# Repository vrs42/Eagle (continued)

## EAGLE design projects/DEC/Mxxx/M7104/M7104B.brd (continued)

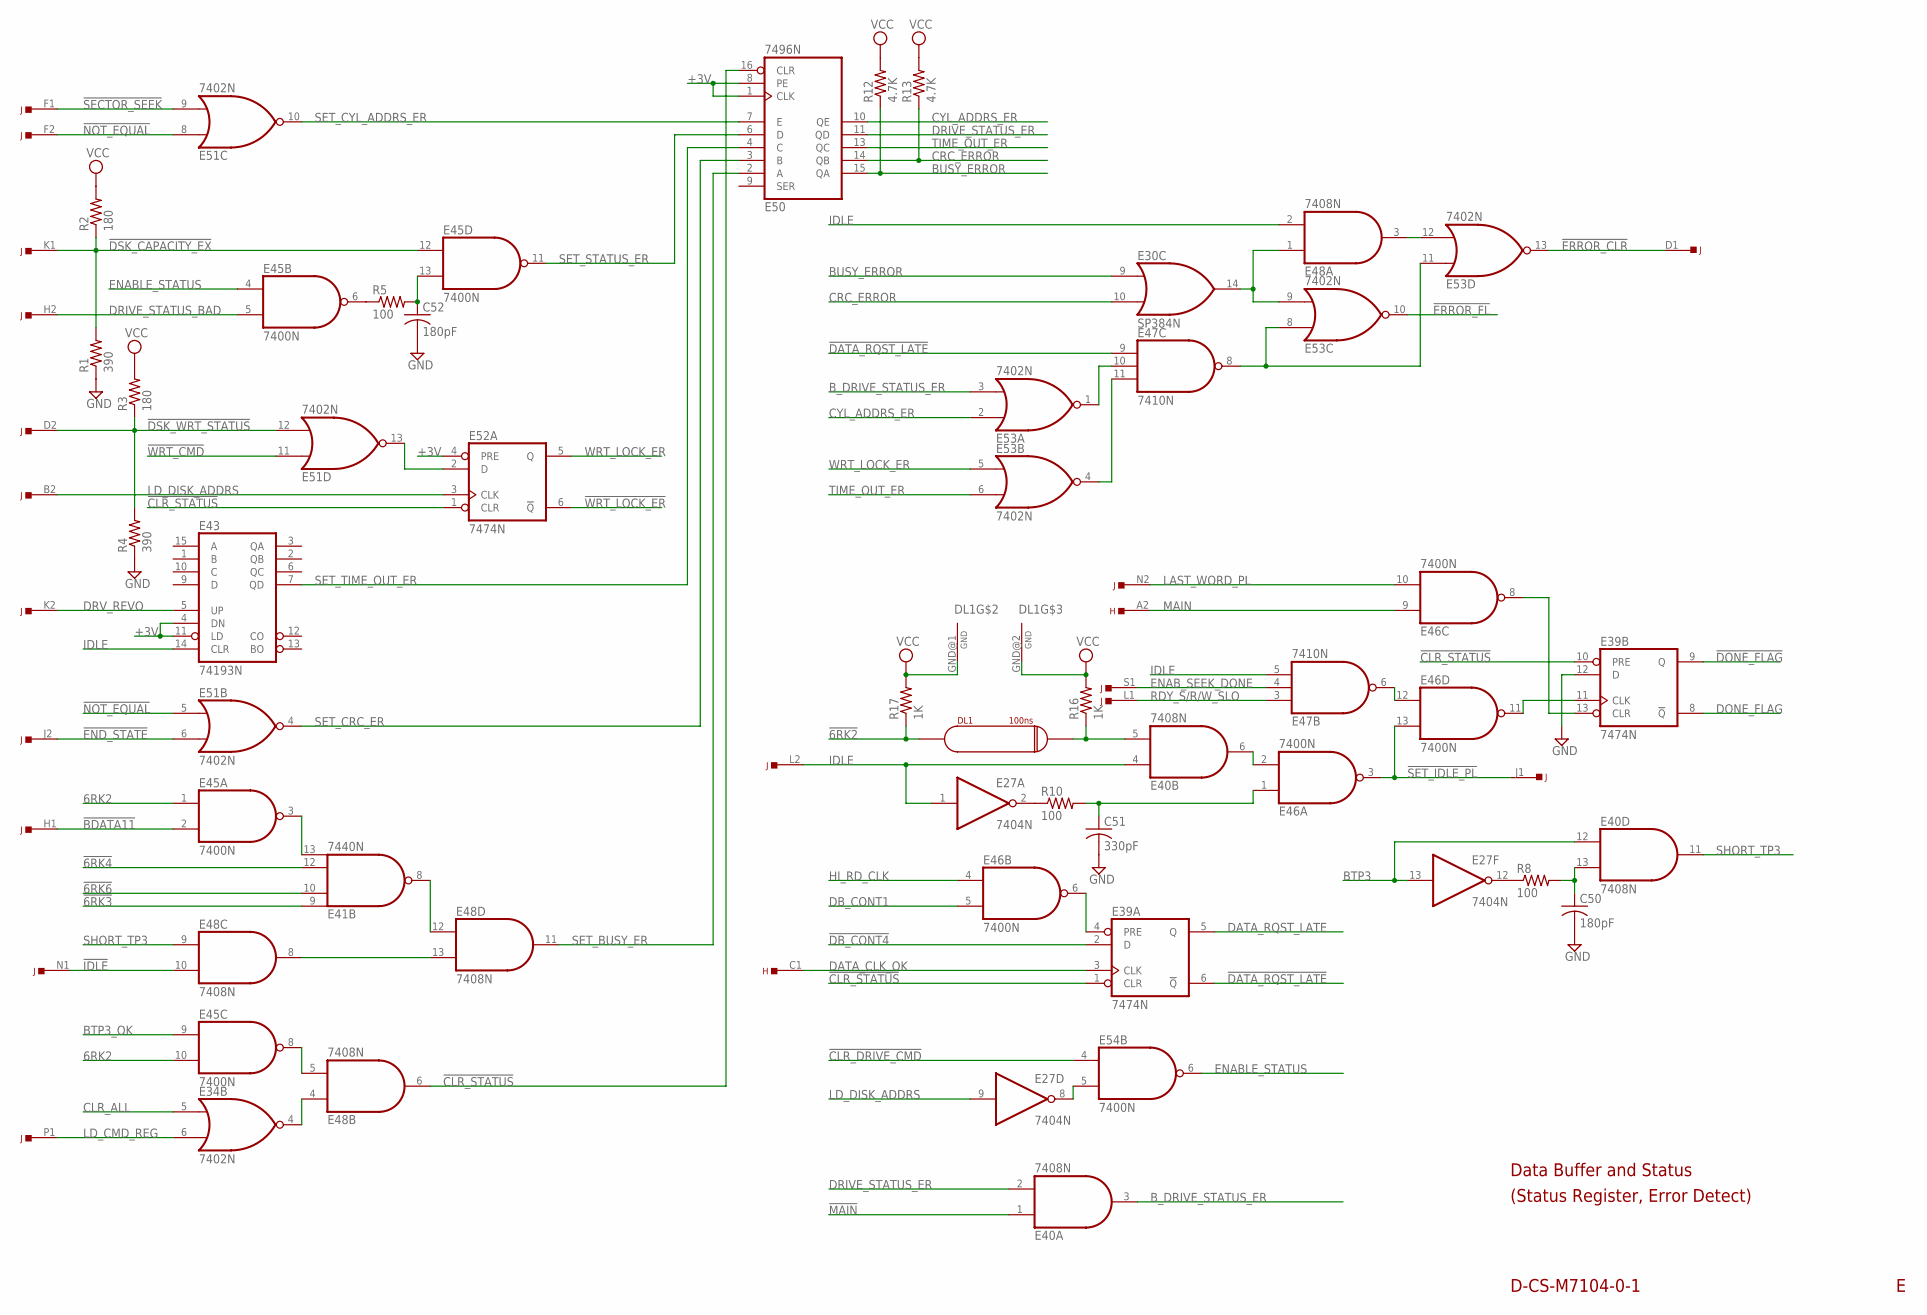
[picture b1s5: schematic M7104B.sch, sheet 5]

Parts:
C50, C52: 180pF; C063-025X075
C51: 330pF; C063-025X075
DL1: 100ns; RCL-L-XX-22
E27: 7404N; DIL14
E30: SP384N; DIL14
E34, E51, E53: 7402N; DIL14
E39, E52: 7474N; DIL14
E40, E48: 7408N; DIL14
E41: 7440N; DIL14
E43: 74193N; DIL16
E45, E46, E54: 7400N; DIL14
E47: 7410N; DIL14
E50: 7496N; DIL16
H: EDGE-TOP; EDGE-CON2
J: EDGE-TOP; EDGE-CON2
R1, R4: 390; 0207/10
R2, R3: 180; 0207/10
R5, R8, R10: 100; 0207/10
R12, R13: 4.7K; 0207/10
R16, R17: 1K; 0207/10

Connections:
6RK2: E45.1 (I0), E45.10 (I1); also elsewhere on the board
!6RK2: DL1.IN, R17.1; also elsewhere on the board
!6RK3: E41.9 (I0); also elsewhere on the board
!6RK4: E41.12 (I2); also elsewhere on the board
!6RK6: E41.10 (I1); also elsewhere on the board
!BDATA11: E45.2 (I1), J.H1; also elsewhere on the board
!CLR_DRIVE_CMD: E54.4 (I0); also elsewhere on the board
!CLR_STATUS: E39.1 (CLR), E39.10 (PRE), E48.6 (O), E50.16 (CLR), E52.1 (CLR)
!DATA_RQST_LATE: E39.6 (!Q), E47.9 (I0)
!DB_CONT4: E39.2 (D); also elsewhere on the board
!DONE_FLAG: E39.9 (Q); also elsewhere on the board
!DSK_CAPACITY_EX: E45.12 (I0), J.K1, R1.2, R2.1
!DSK_WRT_STATUS: E51.12 (I1), J.D2, R3.1, R4.2
!END_STATE: E51.6 (I1), J.J2
!ERROR_CLR: E53.13 (O), J.D1
!ERROR_FL: E53.10 (O); also elsewhere on the board
!IDLE: E48.10 (I1), J.N1; also elsewhere on the board
!MAIN: E40.1 (I0); also elsewhere on the board
!NOT_EQUAL: E51.5 (I0), E51.8 (I0), J.F2
!SECTOR_SEEK: E51.9 (I1), J.F1
!SET_IDLE_PL: E46.3 (O), E46.13 (I1), J.J1
!WRT_CMD: E51.11 (I0); also elsewhere on the board
!WRT_LOCK_ER: E52.6 (!Q)
+3V: E43.4 (DN), E43.11 (LD), E50.1 (CLK), E50.8 (PE), E52.4 (PRE); also elsewhere on the board
BTP3: E27.13 (I), E40.12 (I0); also elsewhere on the board
BTP3_OK: E45.9 (I0); also elsewhere on the board
BUSY_ERROR: E30.9 (I0), E50.15 (QA), R12.1; also elsewhere on the board
B_DRIVE_STATUS_ER: E40.3 (O), E53.3 (I1)
CLR_ALL: E34.5 (I0); also elsewhere on the board
CRC_ERROR: E30.10 (I1), E50.14 (QB), R13.1; also elsewhere on the board
CYL_ADDRS_ER: E50.10 (QE), E53.2 (I0); also elsewhere on the board
DATA_CLK_OK: E39.3 (CLK), H.C1
DATA_RQST_LATE: E39.5 (Q); also elsewhere on the board
DB_CONT1: E46.5 (I1); also elsewhere on the board
DONE_FLAG: E39.8 (!Q); also elsewhere on the board
DRIVE_STATUS_BAD: E45.5 (I1), J.H2
DRIVE_STATUS_ER: E40.2 (I1), E50.11 (QD); also elsewhere on the board
DRV_REVO: E43.5 (UP), J.K2
ENABLE_STATUS: E45.4 (I0), E54.6 (O)
ENAB_SEEK_DONE: E47.4 (I1), J.S1
GND: C50.2, C51.2, C52.2, E27.7 (GND), E30.1 (GND), E34.7 (GND), E39.7 (GND), E39.12 (D), E40.7 (GND), E41.7 (GND), E43.8 (GND), E45.7 (GND), E46.7 (GND), E47.7 (GND), E48.7 (GND), E50.12 (GND), E51.7 (GND), E52.7 (GND), E53.7 (GND), E54.7 (GND), R1.1, R4.1; also elsewhere on the board
HI_RD_CLK: E46.4 (I0); also elsewhere on the board
IDLE: E27.1 (I), E40.4 (I0), E43.14 (CLR), E47.5 (I2), E48.2 (I1), J.L2; also elsewhere on the board
LAST_WORD_PL: E46.10 (I1), J.N2
LD_CMD_REG: E34.6 (I1), J.P1
LD_DISK_ADDRS: E27.9 (I), E52.3 (CLK), J.B2
MAIN: E46.9 (I0), H.A2; also elsewhere on the board
unnamed: E45.6 (O), R5.1
unnamed: C52.1, E45.13 (I1), R5.2
unnamed: C51.1, E46.1 (I0), R10.2
unnamed: E51.13 (O), E52.2 (D)
unnamed: E41.13 (I3), E45.3 (O)
unnamed: E41.8 (O), E48.12 (I0)
unnamed: E40.6 (O), E46.2 (I1)
unnamed: DL1.OUT, E40.5 (I1), R16.1
unnamed: E48.8 (O), E48.13 (I1)
unnamed: E45.8 (O), E48.5 (I1)
unnamed: E34.4 (O), E48.4 (I0)
unnamed: E47.11 (I2), E53.4 (O)
unnamed: E47.10 (I1), E53.1 (O)
unnamed: E30.14 (O), E48.1 (I0), E53.9 (I1)
unnamed: E47.8 (O), E53.8 (I0), E53.11 (I0)
unnamed: E48.3 (O), E53.12 (I1)
unnamed: E27.2 (O), R10.1
unnamed: E46.12 (I0), E47.6 (O)
unnamed: E39.11 (CLK), E46.11 (O)
unnamed: E39.13 (CLR), E46.8 (O)
unnamed: E39.4 (PRE), E46.6 (O)
unnamed: E27.8 (O), E54.5 (I1)
unnamed: E27.12 (O), R8.1
unnamed: C50.1, E40.13 (I1), R8.2
RDY_S/R/W_SLO: E47.3 (I0), J.L1
SET_BUSY_ER: E48.11 (O), E50.2 (A)
SET_CRC_ER: E50.3 (B), E51.4 (O)
SET_CYL_ADDRS_ER: E50.7 (E), E51.10 (O)
SET_STATUS_ER: E45.11 (O), E50.6 (D)
SET_TIME_OUT_ER: E43.7 (QD), E50.4 (C)
SHORT_TP3: E40.11 (O), E48.9 (I0)
TIME_OUT_ER: E50.13 (QC), E53.6 (I1); also elsewhere on the board
VCC: DL1.GND@1 (GND), DL1.GND@2 (GND), E27.14 (VCC), E30.8 (VCC), E34.14 (VCC), E39.14 (VCC), E40.14 (VCC), E41.14 (VCC), E43.16 (VCC), E45.14 (VCC), E46.14 (VCC), E47.14 (VCC), E48.14 (VCC), E50.5 (VCC), E51.14 (VCC), E52.14 (VCC), E53.14 (VCC), E54.14 (VCC), R2.2, R3.2, R12.2, R13.2, R16.2, R17.2; also elsewhere on the board
WRT_LOCK_ER: E52.5 (Q), E53.5 (I0); also elsewhere on the board

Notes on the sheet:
Data Buffer and Status
D-CS-M7104-0-1
(Status Register, Error Detect)

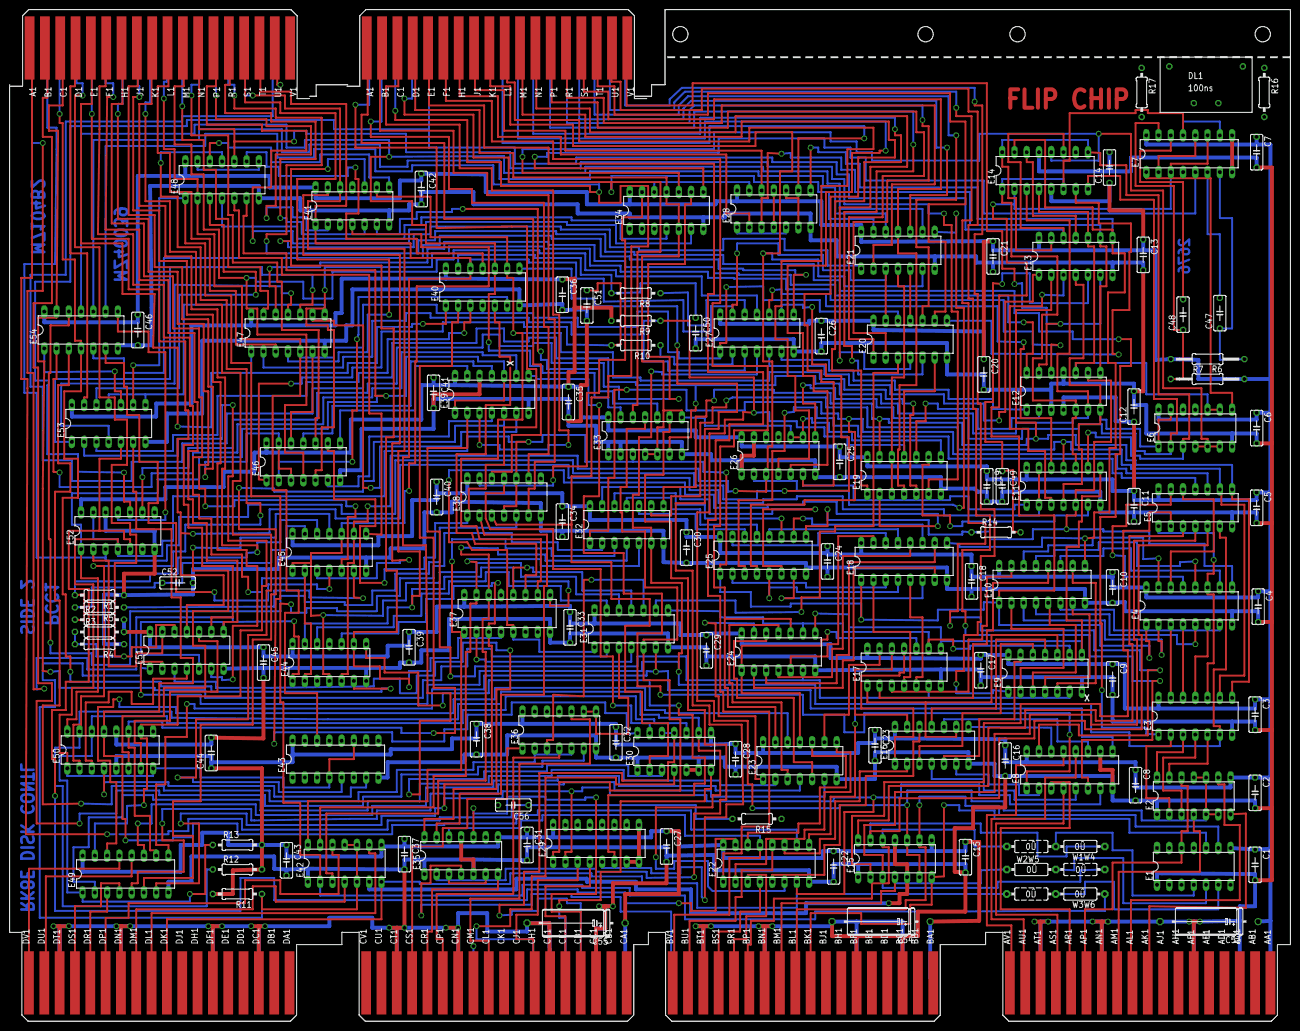
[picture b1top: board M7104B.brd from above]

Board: 4 copper layers, 265.3 x 209.6 mm, 134 parts (0 on the bottom side), 292 nets.

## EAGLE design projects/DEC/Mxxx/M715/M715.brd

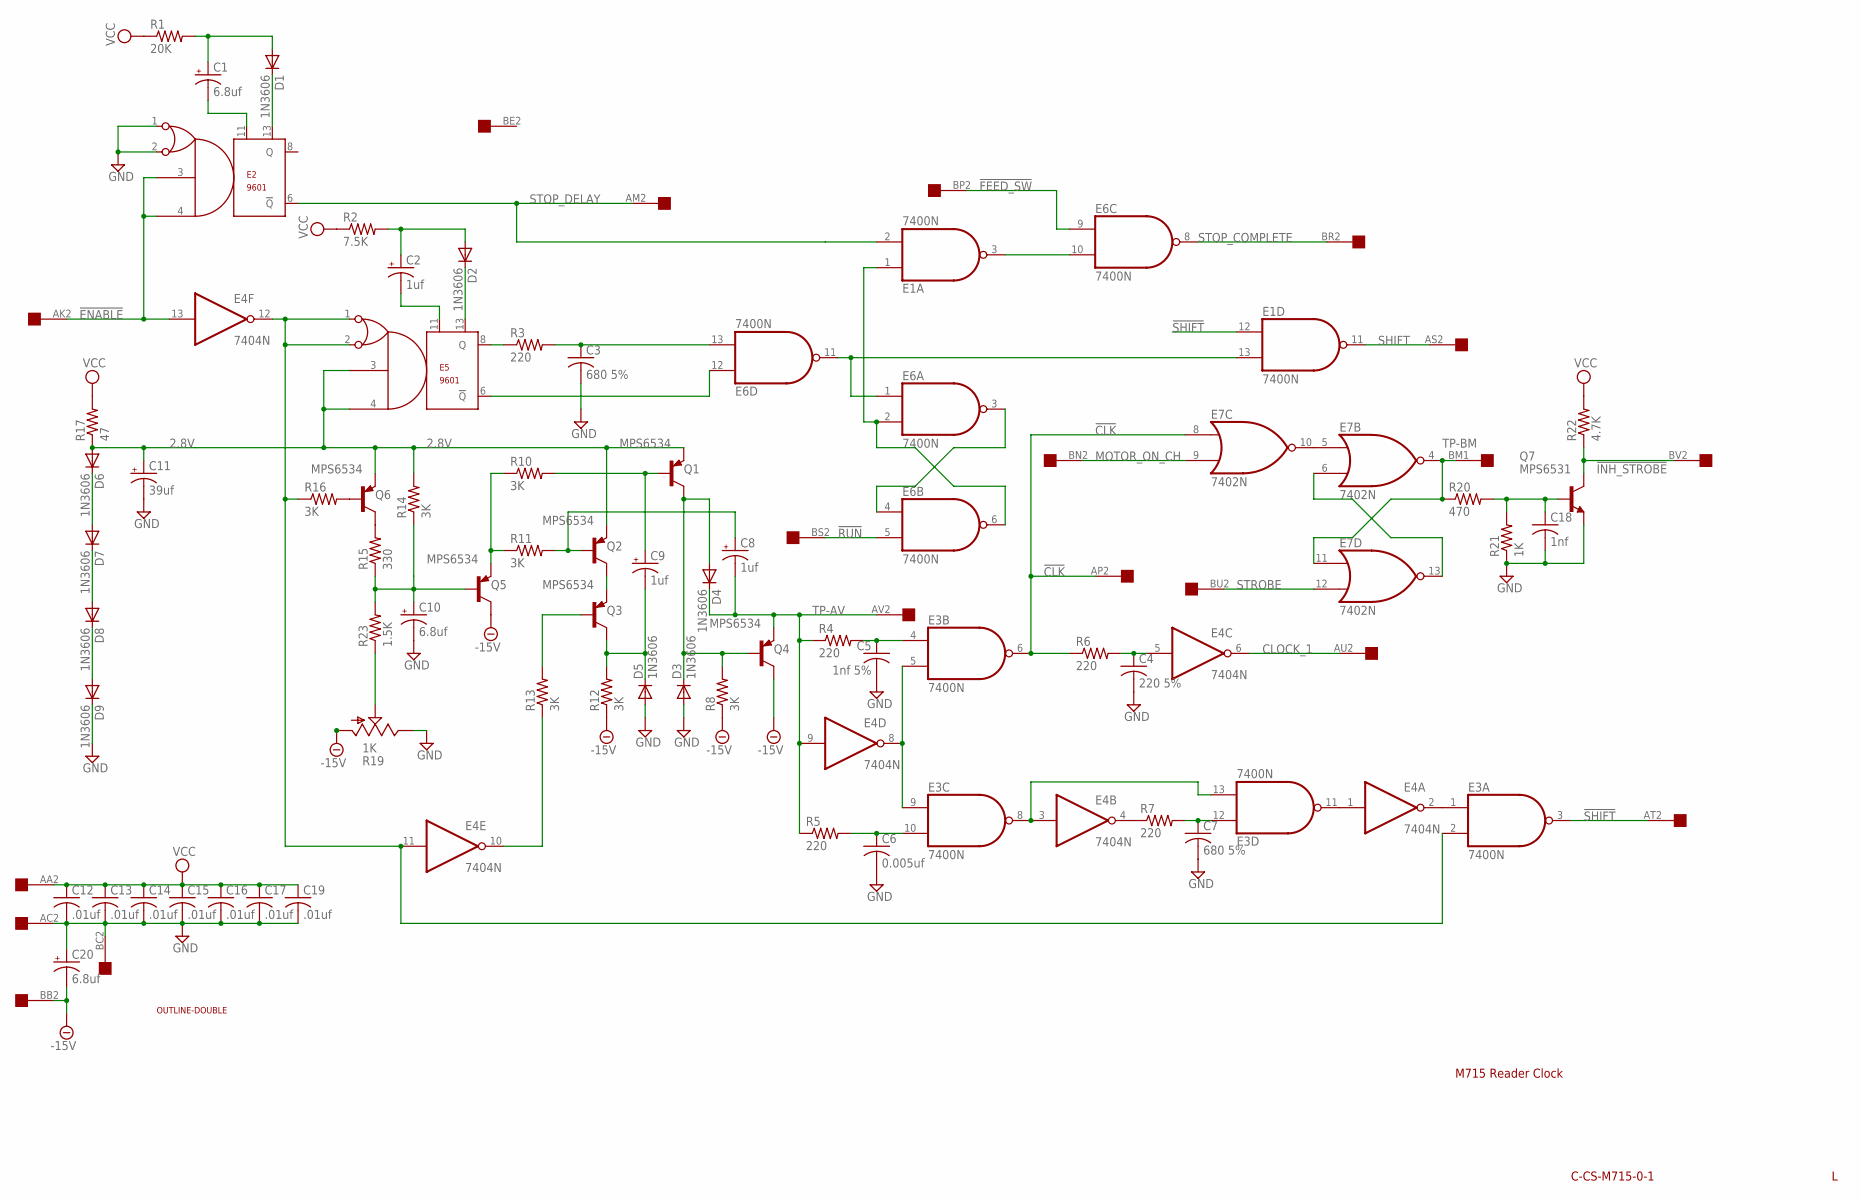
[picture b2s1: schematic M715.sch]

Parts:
C1, C10, C20: 6.8uf; E22-6
C2, C8, C9: 1uf; E15-5
C3, C7: 680 5%; C050-025X075
C4: 220 5%; C050-025X075
C5: 1nf 5%; C050-025X075
C6: 0.005uf; C050-025X075
C11: 39uf; E22-6
C12, C13, C14, C15, C16, C17, C19: .01uf; C050-025X075
C18: 1nf; C050-025X075
D1, D2, D3, D4, D5, D6, D7, D8, D9: 1N3606; DO35-10
E1, E3, E6: 7400N; DIL14
E2, E5: 9601; DIL14
E4: 7404N; DIL14
E7: 7402N; DIL14
Q1, Q2, Q3, Q4, Q5, Q6: MPS6534; TO92
Q7: MPS6531; TO92
R1: 20K; 0207/10
R2: 7.5K; 0207/10
R3, R4, R5, R6, R7: 220; 0207/10
R8, R10, R11, R12, R13, R14, R16: 3K; 0207/10
R15: 330; 0207/10
R17: 47; 0207/10
R19: 1K; PT-SPIN
R20: 470; 0207/10
R21: 1K; 0207/10
R22: 4.7K; 0207/10
R23: 1.5K; 0207/10
U$1: DOUBLE; EDGE-CON4
U$2: OUTLINE-DOUBLE; DOUBLE

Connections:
2.8V: C11.+, D6.A, E5.3, E5.4, Q1.1 (E), Q2.1 (E), Q6.1 (E), R14.2, R17.1
!CLK: E3.6 (O), E7.8 (I0), R6.1, U$1.AP2
!ENABLE: E2.3, E2.4, E4.13 (I), U$1.AK2
!FEED_SW: E6.9 (I0), U$1.BP2
!INH_STROBE: Q7.3 (C), R22.1, U$1.BV2
!RUN: E6.5 (I1), U$1.BS2
!SHIFT: E1.12 (I0), E3.3 (O), U$1.AT2
-15V: C20.-, Q4.3 (C), Q5.3 (C), R8.1, R12.1, R19.A, U$1.BB2
CLOCK_1: E4.6 (O), U$1.AU2
GND: C3.2, C4.2, C5.2, C6.2, C7.2, C10.-, C11.-, C12.2, C13.2, C14.2, C15.2, C16.2, C17.2, C18.2, C19.2, C20.+, D3.A, D5.A, D9.C, E1.7 (GND), E2.1, E2.2, E2.7 (GND), E3.7 (GND), E4.7 (GND), E5.7 (GND), E6.7 (GND), E7.7 (GND), Q7.1 (E), R19.E, R21.1, U$1.AC2, U$1.BC2
MOTOR_ON_CH: E7.9 (I1), U$1.BN2
unnamed: E6.3 (O), E6.4 (I0)
unnamed: E1.1 (I0), E6.2 (I1), E6.6 (O)
unnamed: E1.13 (I1), E6.1 (I0), E6.11 (O)
unnamed: E3.1 (I0), E4.2 (O)
unnamed: E7.6 (I1), E7.13 (O)
unnamed: E1.3 (O), E6.10 (I1)
unnamed: Q6.2 (B), R16.2
unnamed: E7.5 (I0), E7.10 (O)
unnamed: E3.2 (I1), E4.11 (I), E4.12 (O), E5.1, E5.2, R16.1
unnamed: E3.5 (I1), E3.9 (I0), E4.8 (O)
unnamed: E3.11 (O), E4.1 (I)
unnamed: E3.8 (O), E3.13 (I1), E4.3 (I)
unnamed: C7.1, E3.12 (I0), R7.2
unnamed: E4.4 (O), R7.1
unnamed: R19.S, R23.1
unnamed: C4.1, E4.5 (I), R6.2
unnamed: C18.1, Q7.2 (B), R20.2, R21.2
unnamed: C6.1, E3.10 (I1), R5.2
unnamed: C5.1, E3.4 (I0), R4.2
unnamed: D6.C, D7.A
unnamed: D7.C, D8.A
unnamed: D8.C, D9.A
unnamed: Q6.3 (C), R15.2
unnamed: C10.+, Q5.2 (B), R14.1, R15.1, R23.2
unnamed: Q5.1 (E), R10.1, R11.1
unnamed: Q2.3 (C), Q3.1 (E)
unnamed: C8.+, Q2.2 (B), R11.2
unnamed: E4.10 (O), R13.1
unnamed: Q3.2 (B), R13.2
unnamed: C9.-, D5.C, Q3.3 (C), R12.2
unnamed: C9.+, Q1.2 (B), R10.2
unnamed: D3.C, D4.A, Q1.3 (C), Q4.2 (B), R8.2
unnamed: D1.C, E2.13
unnamed: C1.-, E2.11
unnamed: C1.+, D1.A, R1.2
unnamed: D2.C, E5.13
unnamed: C2.-, E5.11
unnamed: C2.+, D2.A, R2.2
unnamed: E5.6 (!Q), E6.12 (I0)
unnamed: E5.8 (Q), R3.1
unnamed: C3.1, E6.13 (I1), R3.2
SHIFT: E1.11 (O), U$1.AS2
STOP_COMPLETE: E6.8 (O), U$1.BR2
STOP_DELAY: E1.2 (I1), E2.6 (!Q), U$1.AM2
STROBE: E7.12 (I1), U$1.BU2
TP-AV: C8.-, D4.C, E4.9 (I), Q4.1 (E), R4.1, R5.1, U$1.AV2
TP-BM: E7.4 (O), E7.11 (I0), R20.1, U$1.BM1
VCC: C12.1, C13.1, C14.1, C15.1, C16.1, C17.1, C19.1, E1.14 (VCC), E2.14 (VCC), E3.14 (VCC), E4.14 (VCC), E5.14 (VCC), E6.14 (VCC), E7.14 (VCC), R1.1, R2.1, R17.2, R22.2, U$1.AA2

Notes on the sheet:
M715 Reader Clock
C-CS-M715-0-1

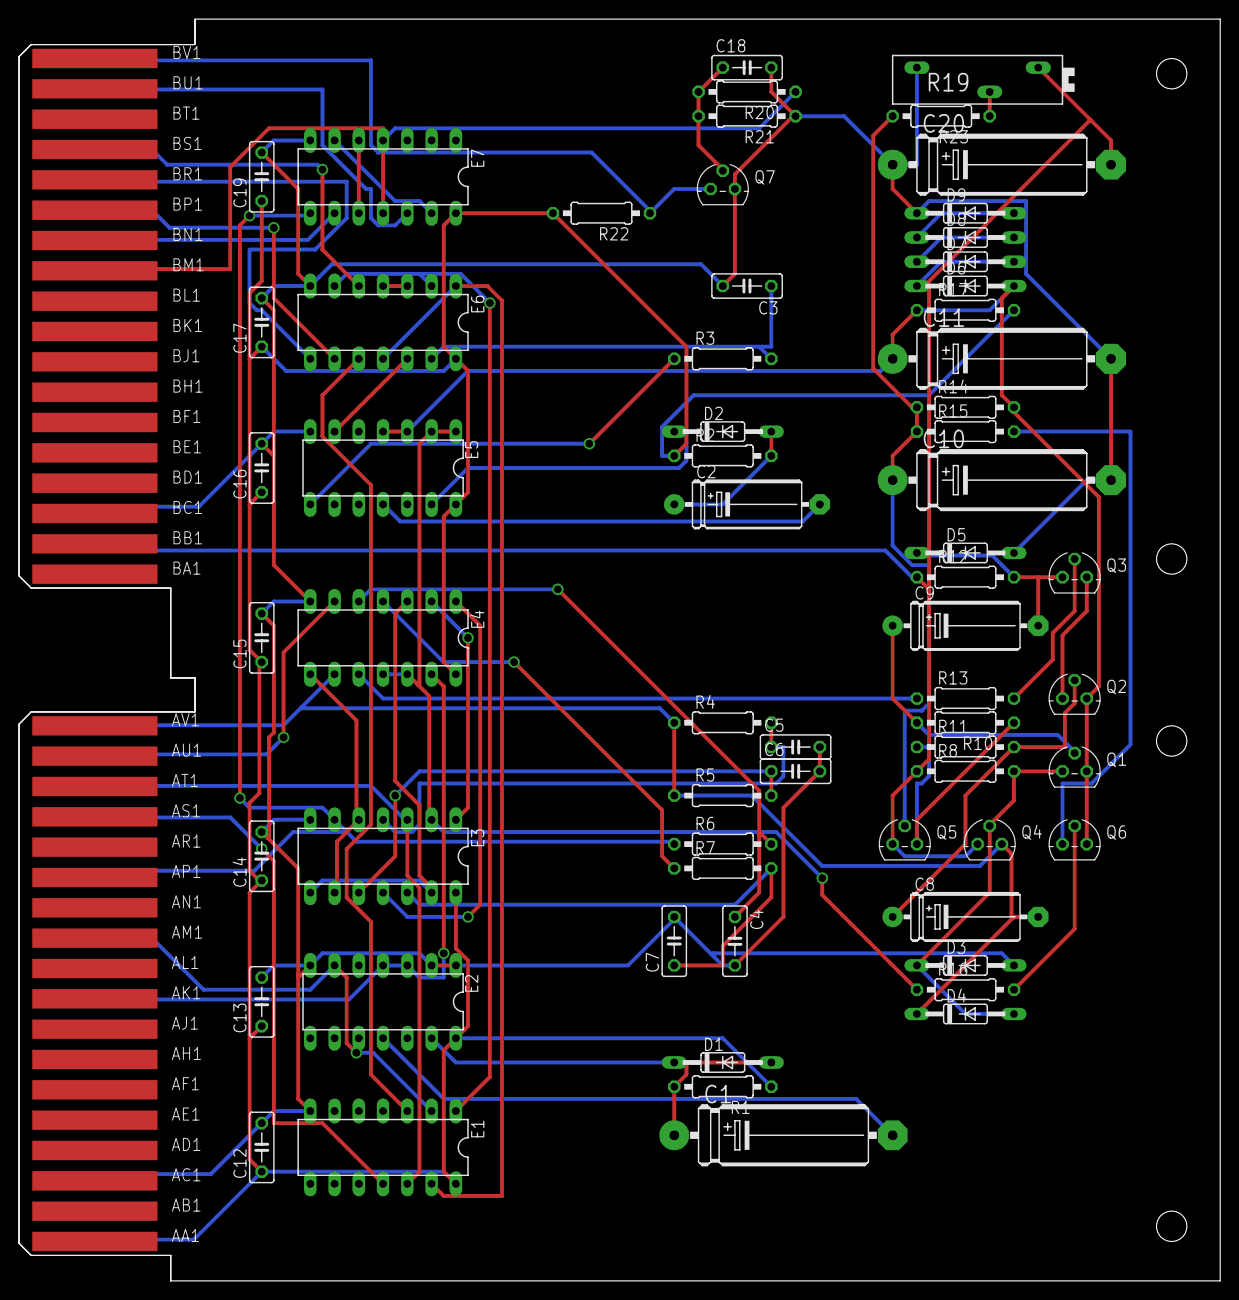
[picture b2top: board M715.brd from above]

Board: 2 copper layers, 125.7 x 132.1 mm, 66 parts (0 on the bottom side), 59 nets.

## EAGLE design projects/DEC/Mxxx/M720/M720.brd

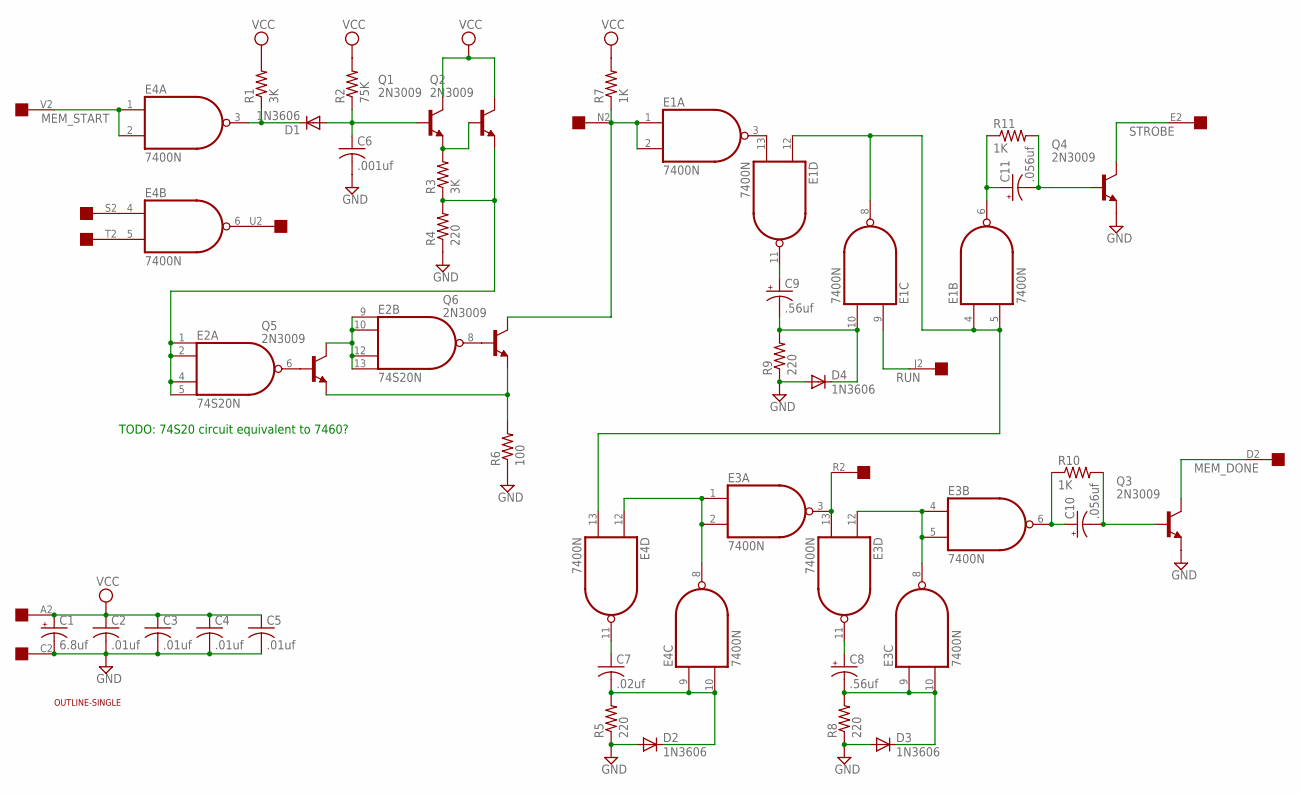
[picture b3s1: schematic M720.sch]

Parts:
C1: 6.8uf; E15-5
C2, C3, C4, C5: .01uf; C050-025X075
C6: .001uf; C050-025X075
C7: .02uf; C050-025X075
C8, C9: .56uf; B45181C
C10, C11: .056uf; B45181C
D1, D2, D3, D4: 1N3606; DO35-10
E1, E3, E4: 7400N; DIL14
E2: 74S20N; DIL14
Q1, Q2, Q3, Q4, Q5, Q6: 2N3009; TO5
R1, R3: 3K; 0207/10
R2: 75K; 0207/10
R4, R5, R8, R9: 220; 0207/10
R6: 100; 0207/10
R7, R10, R11: 1K; 0207/10
U$1: OUTLINE-SINGLE; SINGLE
U$3: EDGE-1; EDGE-CON1

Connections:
GND: C1.-, C2.2, C3.2, C4.2, C5.2, C6.2, D2.A, D3.A, D4.A, E1.7 (GND), E2.7 (GND), E3.7 (GND), E4.7 (GND), Q3.1 (E), Q4.1 (E), R4.1, R5.1, R6.1, R8.1, R9.1, U$3.C2
MEM_DONE: Q3.3 (C), U$3.D2
MEM_START: E4.1 (I0), E4.2 (I1), U$3.V2
unnamed: E2.1 (I0), E2.2 (I1), E2.4 (I2), E2.5 (I3), Q2.1 (E), R3.1, R4.2
unnamed: D1.C, E4.3 (O), R1.1
unnamed: C6.1, D1.A, Q1.2 (B), R2.1
unnamed: Q1.1 (E), Q2.2 (B), R3.2
unnamed: E4.4 (I0), U$3.S2
unnamed: E4.5 (I1), U$3.T2
unnamed: E4.6 (O), U$3.U2
unnamed: E1.1 (I0), E1.2 (I1), Q6.3 (C), R7.1, U$3.N2
unnamed: E1.3 (O), E1.13 (I1)
unnamed: E1.4 (I0), E1.5 (I1), E1.8 (O), E1.12 (I0), E4.13 (I1)
unnamed: C7.2, D2.C, E4.9 (I0), E4.10 (I1), R5.2
unnamed: C9.+, E1.11 (O)
unnamed: C9.-, D4.C, E1.10 (I1), R9.2
unnamed: C11.+, E1.6 (O), R11.1
unnamed: C11.-, Q4.2 (B), R11.2
unnamed: E3.1 (I0), E3.2 (I1), E4.8 (O), E4.12 (I0)
unnamed: C7.1, E4.11 (O)
unnamed: E3.3 (O), E3.13 (I1), U$3.R2
unnamed: E3.4 (I0), E3.5 (I1), E3.8 (O), E3.12 (I0)
unnamed: E2.8 (O), Q6.2 (B)
unnamed: C8.-, D3.C, E3.9 (I0), E3.10 (I1), R8.2
unnamed: C8.+, E3.11 (O)
unnamed: C10.+, E3.6 (O), R10.1
unnamed: C10.-, Q3.2 (B), R10.2
unnamed: E2.6 (O), Q5.2 (B)
unnamed: E2.9 (I0), E2.10 (I1), E2.12 (I2), E2.13 (I3), Q5.3 (C)
unnamed: Q5.1 (E), Q6.1 (E), R6.2
RUN: E1.9 (I0), U$3.J2
STROBE: Q4.3 (C), U$3.E2
VCC: C1.+, C2.1, C3.1, C4.1, C5.1, E1.14 (VCC), E2.14 (VCC), E3.14 (VCC), E4.14 (VCC), Q1.3 (C), Q2.3 (C), R1.2, R2.2, R7.2, U$3.A2

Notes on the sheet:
TODO: 74S20 circuit equivalent to 7460?

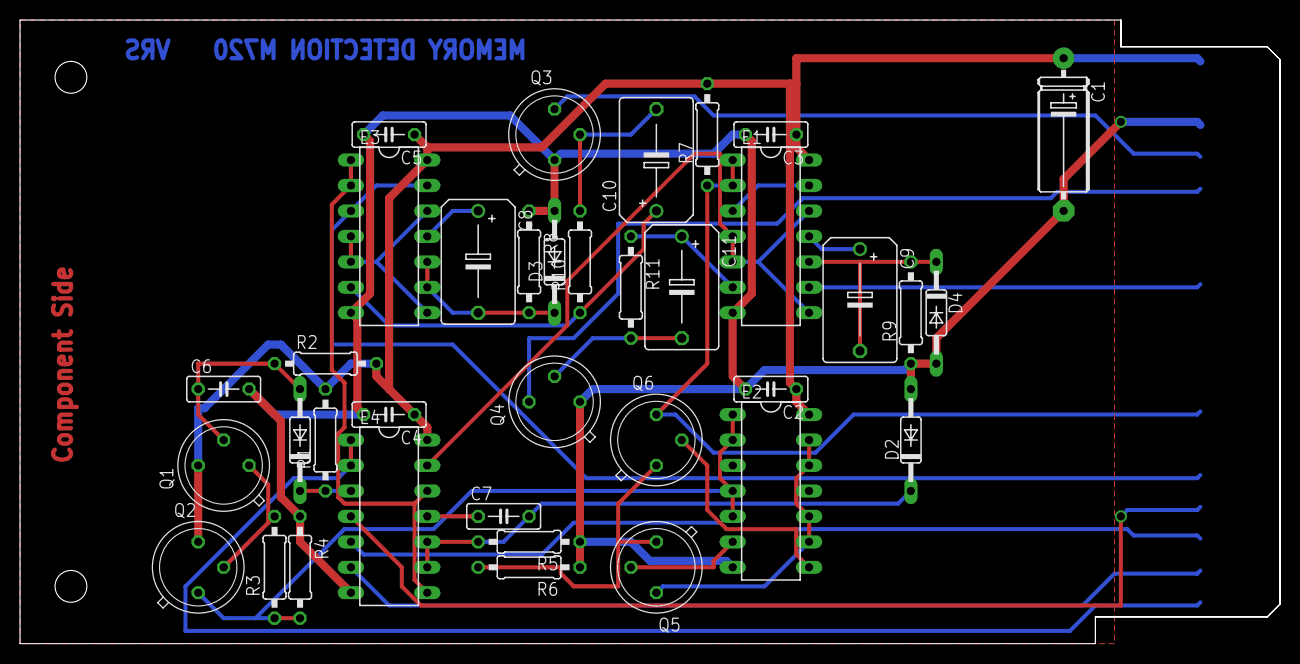
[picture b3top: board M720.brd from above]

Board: 2 copper layers, 125.7 x 62.2 mm, 38 parts (0 on the bottom side), 33 nets.

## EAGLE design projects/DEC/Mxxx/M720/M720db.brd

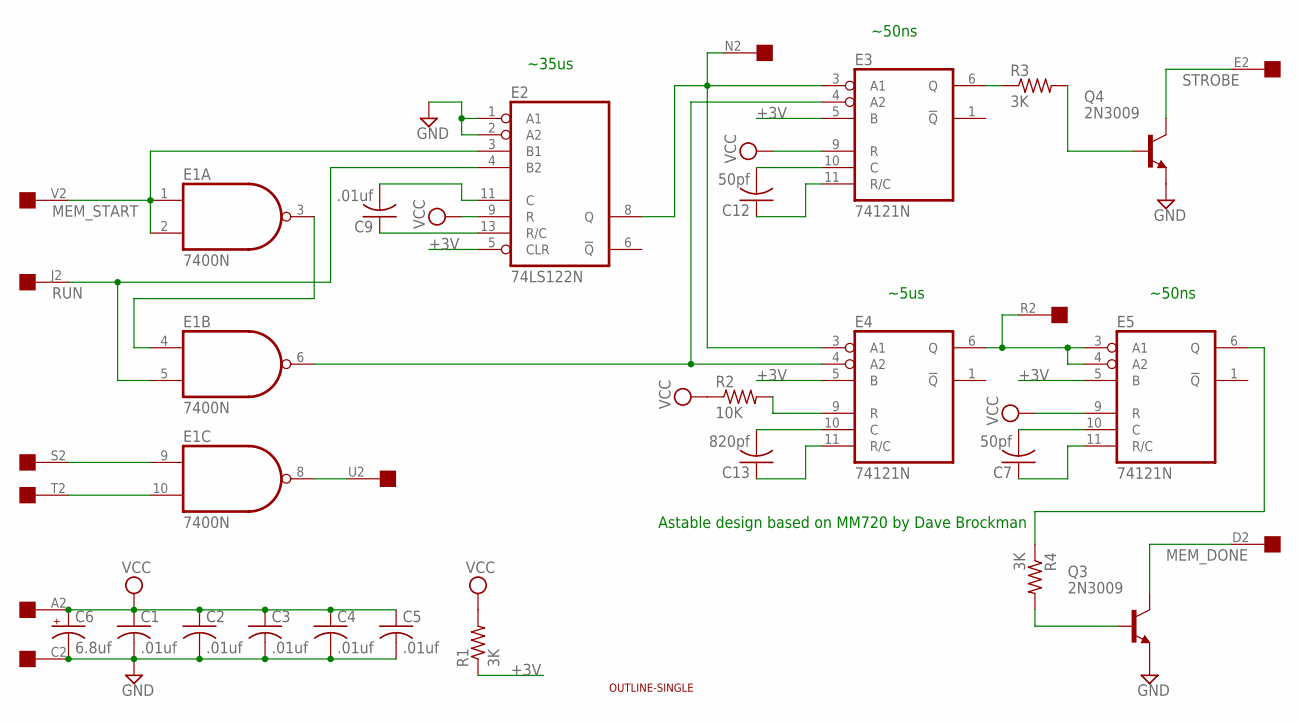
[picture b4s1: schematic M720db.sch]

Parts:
C1, C2, C3, C4, C5, C9: .01uf; C050-025X075
C6: 6.8uf; E15-5
C7, C12: 50pf; C050-025X075
C13: 820pf; C050-025X075
E1: 7400N; DIL14
E2: 74LS122N; DIL14
E3, E4, E5: 74121N; DIL14
Q3, Q4: 2N3009; TO5
R1, R3, R4: 3K; 0207/10
R2: 10K; 0207/10
U$1: OUTLINE-SINGLE; SINGLE
U$3: EDGE-1; EDGE-CON1

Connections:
+3V: E2.5 (CLR), E3.5 (B), E4.5 (B), E5.5 (B), R1.1
GND: C1.2, C2.2, C3.2, C4.2, C5.2, C6.-, E1.7 (GND), E2.1 (A1), E2.2 (A2), E2.7 (GND), E3.7 (GND), E4.7 (GND), E5.7 (GND), Q3.1 (E), Q4.1 (E), U$3.C2
MEM_DONE: Q3.3 (C), U$3.D2
MEM_START: E1.1 (I0), E1.2 (I1), E2.3 (B1), U$3.V2
unnamed: E1.3 (O), E1.4 (I0)
unnamed: E1.6 (O), E3.4 (A2), E4.4 (A2)
unnamed: E2.8 (Q), E3.3 (A1), E4.3 (A1), U$3.N2
unnamed: C9.2, E2.11 (C)
unnamed: E1.9 (I0), U$3.S2
unnamed: E1.10 (I1), U$3.T2
unnamed: E1.8 (O), U$3.U2
unnamed: E4.6 (Q), E5.3 (A1), E5.4 (A2), U$3.R2
unnamed: C7.2, E5.10 (C)
unnamed: C7.1, E5.11 (R/C)
unnamed: E3.6 (Q), R3.1
unnamed: Q4.2 (B), R3.2
unnamed: E5.6 (Q), R4.1
unnamed: C9.1, E2.13 (R/C)
unnamed: Q3.2 (B), R4.2
unnamed: C12.1, E3.11 (R/C)
unnamed: C12.2, E3.10 (C)
unnamed: C13.1, E4.11 (R/C)
unnamed: C13.2, E4.10 (C)
unnamed: E4.9 (R), R2.2
RUN: E1.5 (I1), E2.4 (B2), U$3.J2
STROBE: Q4.3 (C), U$3.E2
VCC: C1.1, C2.1, C3.1, C4.1, C5.1, C6.+, E1.14 (VCC), E2.9 (R), E2.14 (VCC), E3.9 (R), E3.14 (VCC), E4.14 (VCC), E5.9 (R), E5.14 (VCC), R1.2, R2.1, U$3.A2

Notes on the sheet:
~35us
~50ns
~5us
Astable design based on MM720 by Dave Brockman

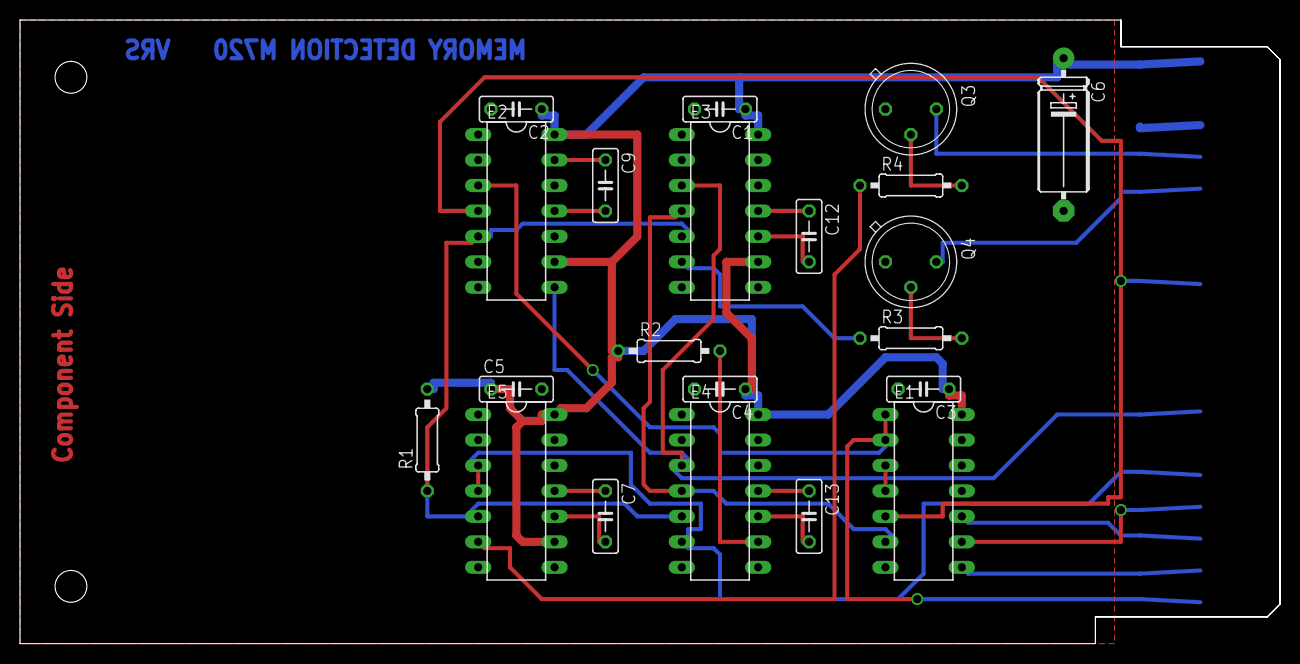
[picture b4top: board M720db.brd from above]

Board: 2 copper layers, 125.7 x 62.2 mm, 23 parts (0 on the bottom side), 27 nets.

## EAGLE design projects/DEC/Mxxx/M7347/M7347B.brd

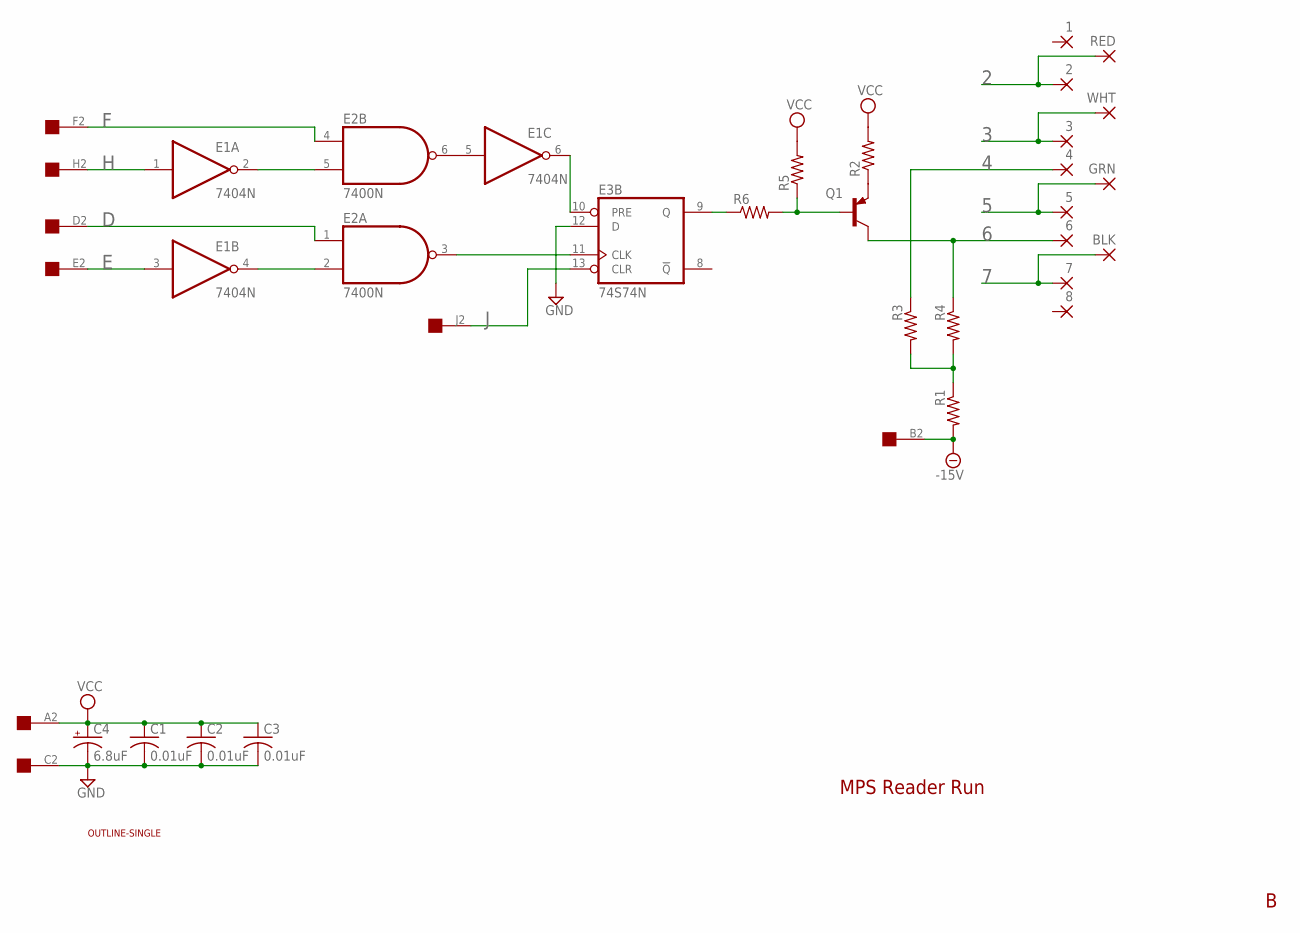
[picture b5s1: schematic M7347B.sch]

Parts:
1, 2, 3, 4, 5, 6, 7, 8: 2,15/1,0
BLK: 2,15/1,0
C1, C2, C3: 0.01uF; C050-025X075
C4: 6.8uF; E12-8
E1: 7404N; DIL14
E2: 7400N; DIL14
E3: 74S74N; DIL14
GRN: 2,15/1,0
Q1: -PNP-TO5; TO5
R1, R2, R3, R4, R5, R6: R-US_0207/10; 0207/10
RED: 2,15/1,0
U$1: EDGE-1; EDGE-CON1
U$2: OUTLINE-SINGLE; SINGLE
WHT: 2,15/1,0

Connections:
2: 2.1, RED.1
3: 3.1, WHT.1
4: 4.1, R3.1
5: 5.1, GRN.1
6: 6.1, Q1.3 (C), R4.1
7: 7.1, BLK.1
-15V: R1.2, U$1.B2
D: E2.1 (I0), U$1.D2
E: E1.3 (I), U$1.E2
F: E2.4 (I0), U$1.F2
GND: C1.2, C2.2, C3.2, C4.-, E1.7 (GND), E2.7 (GND), E3.7 (GND), E3.12 (D), U$1.C2
H: E1.1 (I), U$1.H2
J: E3.13 (CLR), U$1.J2
unnamed: Q1.2 (B), R5.1, R6.2
unnamed: E1.2 (O), E2.5 (I1)
unnamed: E1.4 (O), E2.2 (I1)
unnamed: E1.6 (O), E3.10 (PRE)
unnamed: E2.3 (O), E3.11 (CLK)
unnamed: E1.5 (I), E2.6 (O)
unnamed: E3.9 (Q), R6.1
unnamed: R1.1, R3.2, R4.2
unnamed: Q1.1 (E), R2.1
VCC: C1.1, C2.1, C3.1, C4.+, E1.14 (VCC), E2.14 (VCC), E3.14 (VCC), R2.2, R5.2, U$1.A2

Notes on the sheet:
MPS Reader Run

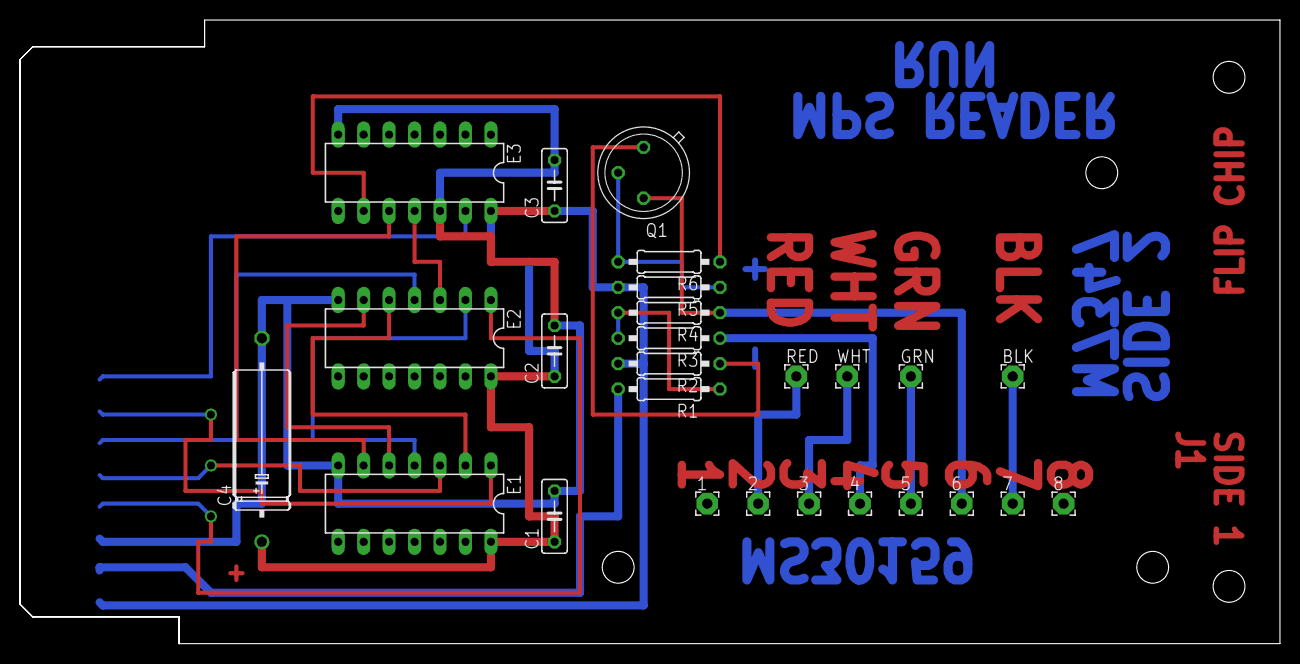
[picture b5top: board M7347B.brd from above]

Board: 2 copper layers, 125.7 x 62.2 mm, 29 parts (0 on the bottom side), 23 nets.

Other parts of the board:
U$3: FLIPCHIP
